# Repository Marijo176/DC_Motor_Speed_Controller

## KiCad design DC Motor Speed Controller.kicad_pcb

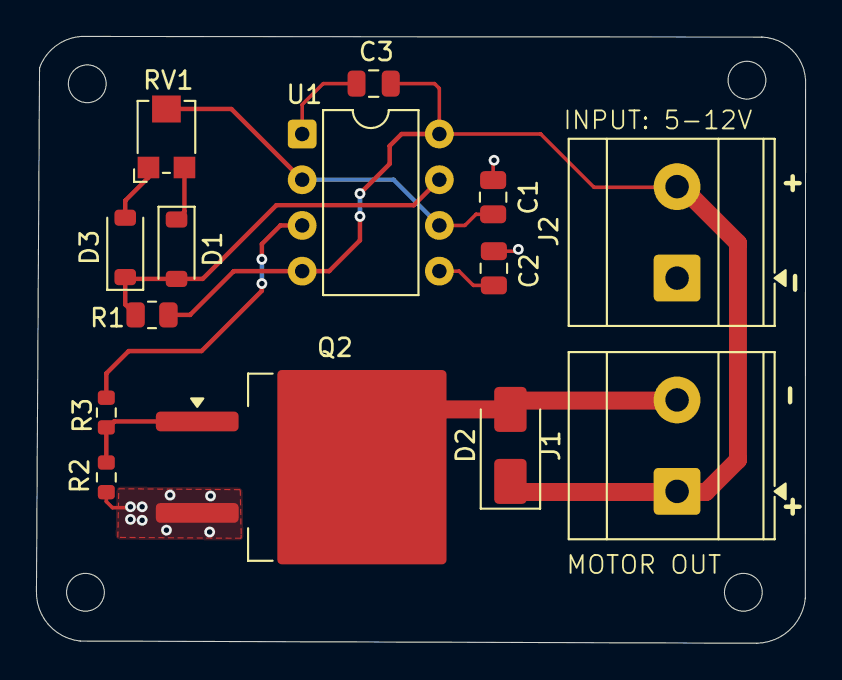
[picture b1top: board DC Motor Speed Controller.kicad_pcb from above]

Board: 2 copper layers, 42.7 x 33.7 mm, 18 parts (0 on the bottom side), 10 nets.

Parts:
C1: 100nF; C_0805_2012Metric
C2: 10 nF; C_0805_2012Metric
C3: 100 nF; C_0805_2012Metric
D1, D3: 1N4148W; D_SOD-123
D2: SS14; D_SMA
H1, H1#2, H1#3, H2: MountingHole; MountingHole_2.1mm
J1, J2: Screw_Terminal_01x02; TerminalBlock_Phoenix_MKDS-3-2-5.08_1x02_P5.08mm_Horizontal
Q2: Q_NMOS_GDS; TO-263-2
R1: 1000r; R_0805_2012Metric
R2: 10000R; R_0603_1608Metric
R3: 100R; R_0603_1608Metric
RV1: 10000; Potentiometer_Bourns_TC33X_Vertical
U1: NE555P; DIP-8_W7.62mm

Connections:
GND: C1.2, C2.2, C3.2, J2.1, Q2.3 (S), R2.2, U1.1 (GND)
unnamed: D1.2 (A), D3.1 (K), R1.2, U1.7 (DISCH)
unnamed: D1.1 (K), RV1.3
unnamed: D2.2 (A), J1.2, Q2.2 (D)
unnamed: C3.1, D2.1 (K), J1.1, J2.2, R1.1, U1.4 (~RST), U1.8 (VCC)
unnamed: D3.2 (A), RV1.1
unnamed: Q2.1 (G), R2.1, R3.2
unnamed: C2.1, U1.5 (CONT)
unnamed: R3.1, U1.3 (OUT)
unnamed: C1.1, RV1.2, U1.2 (TRIG), U1.6 (THRES)
